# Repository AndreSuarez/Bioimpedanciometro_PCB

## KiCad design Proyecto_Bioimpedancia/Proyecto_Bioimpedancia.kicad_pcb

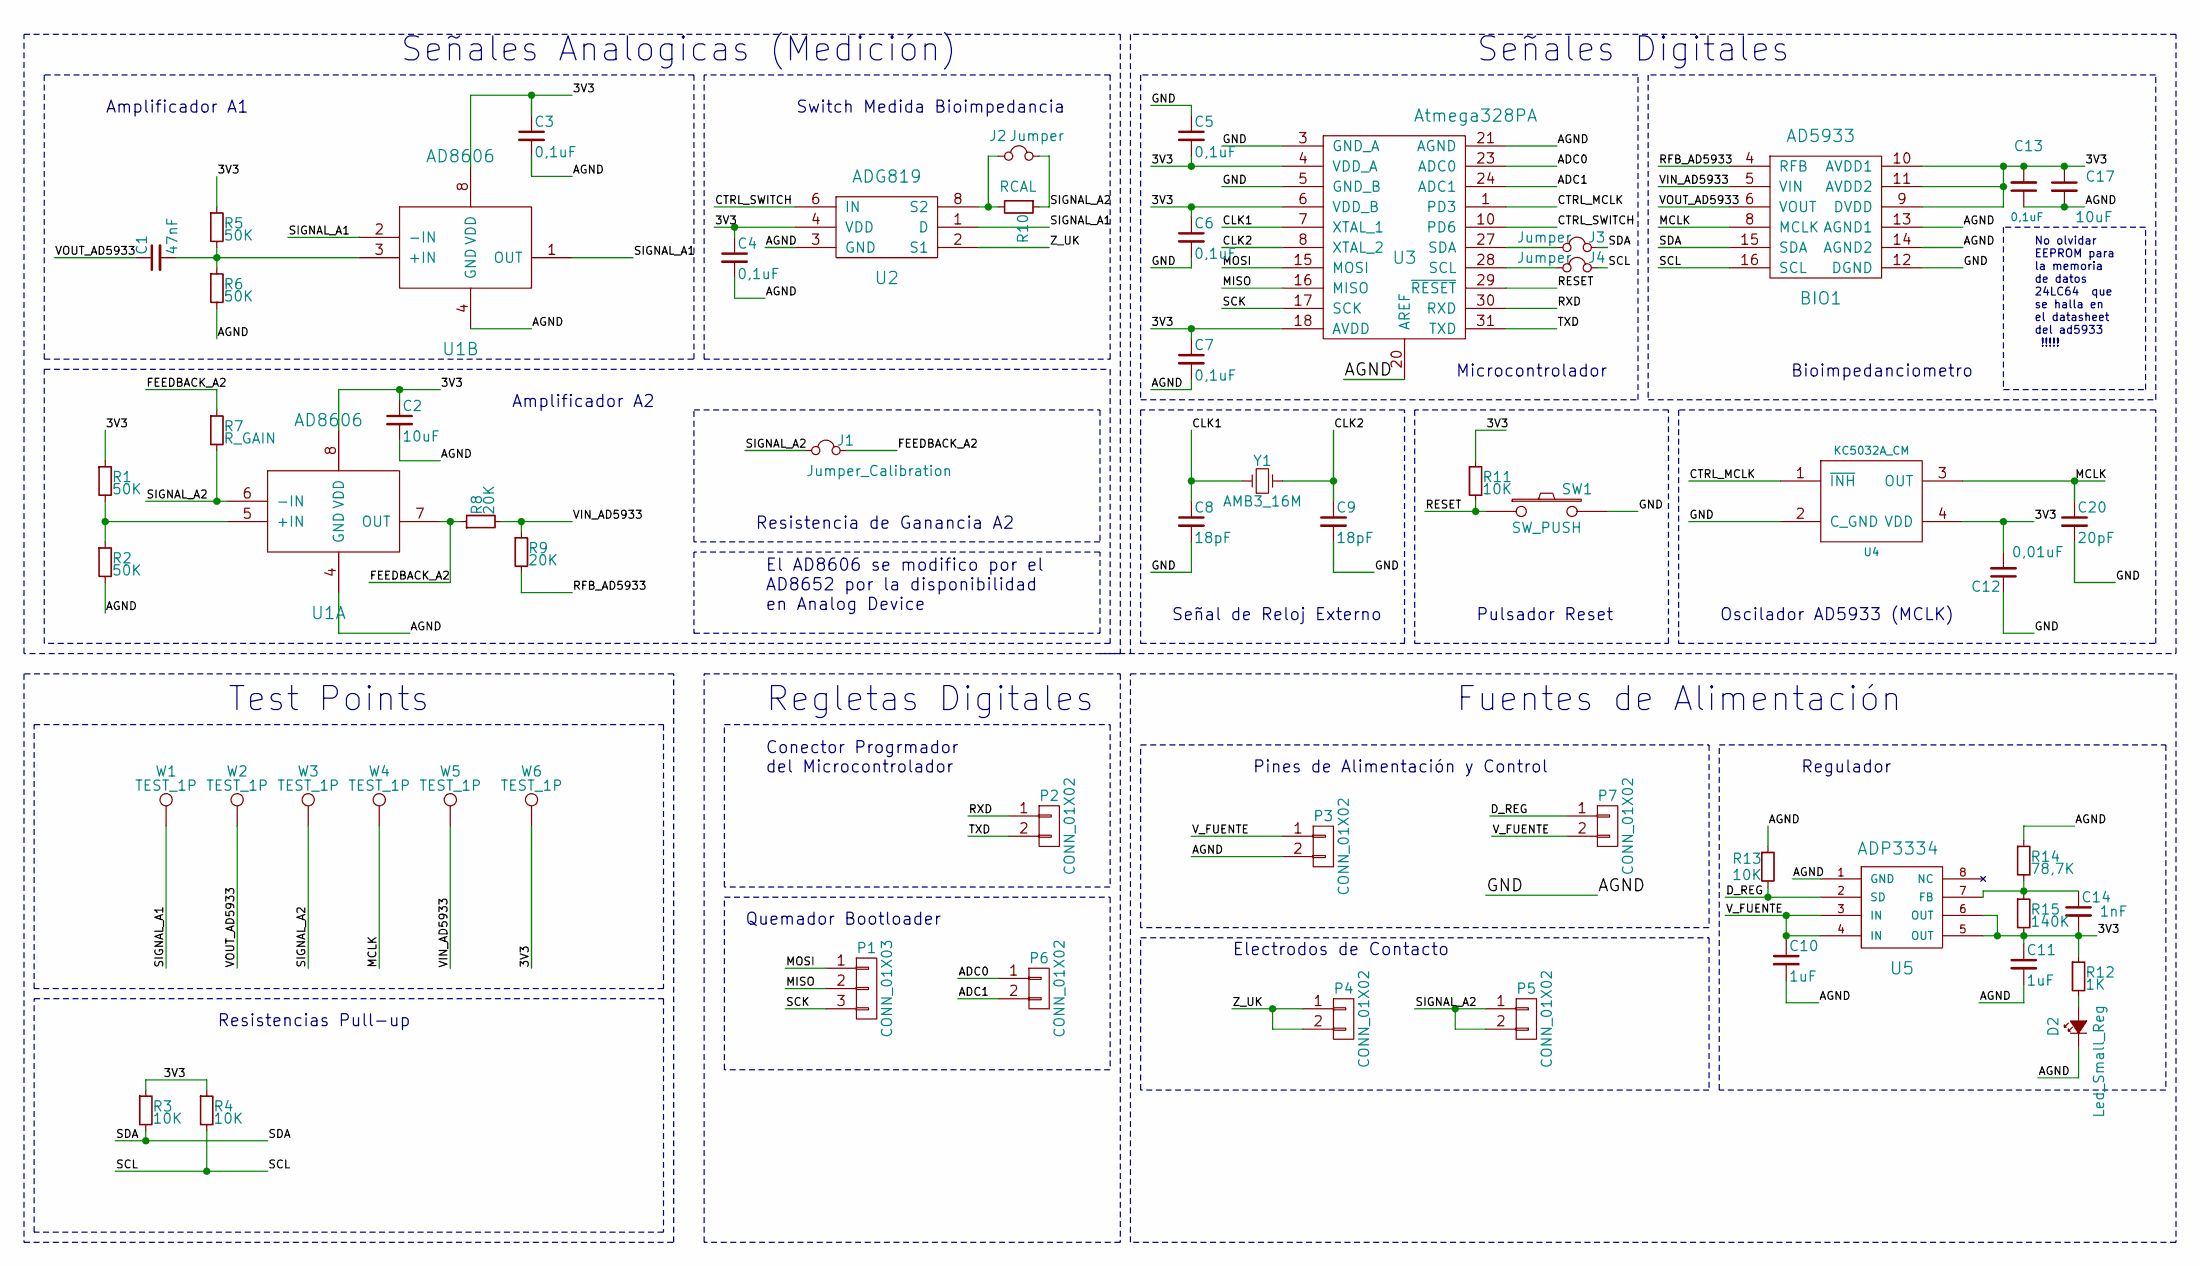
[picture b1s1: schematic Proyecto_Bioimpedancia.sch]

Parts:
BIO1: AD5933; SSOP-16_5.3x6.2mm_Pitch0.65mm
C1: 47nF; C_0805_HandSoldering
C2, C17: 10uF; C_0805_HandSoldering
C3, C4, C5, C6, C7, C13: 0,1uF; C_0805_HandSoldering
C8, C9: 18pF; C_0805_HandSoldering
C10, C11: 1uF; C_0805_HandSoldering
C12: 0,01uF; C_0805_HandSoldering
C14: 1nF; C_1206_HandSoldering
C20: 20pF; C_0805_HandSoldering
D2: Led_Small_Reg; LED_0805
J1: Jumper_Calibration; Pin_Header_Straight_1x02_Pitch2.54mm
J2, J3, J4: Jumper; Pin_Header_Straight_1x02_Pitch2.54mm
P1: CONN_01X03; Socket_Strip_Straight_1x03_Pitch2.54mm
P2, P3, P4, P5, P6, P7: CONN_01X02; Socket_Strip_Straight_1x02_Pitch2.54mm
R1, R2, R5, R6: 50K; R_0805_HandSoldering
R3, R4, R11, R13: 10K; R_0805_HandSoldering
R7: R_GAIN; R_0805_HandSoldering
R8, R9: 20K; R_0805_HandSoldering
R10: RCAL; R_0805_HandSoldering
R12: 1K; R_0805_HandSoldering
R14: 78,7K; R_0805_HandSoldering
R15: 140K; R_0805_HandSoldering
SW1: SW_PUSH; KPT_1187B
U1: AD8606; SOIC-8_3.9x4.9mm_Pitch1.27mm
U2: ADG819; MSOP-8_3x3mm_Pitch0.65mm
U3: Atmega328PA; TQFP-32_7x7mm_Pitch0.8mm
U4: KC5032A_CM
U5: ADP3334; SOIC-8_3.9x4.9mm_Pitch1.27mm
W1, W2, W3, W4, W5, W6: TEST_1P; Measurement_Point_Round-TH_Small
Y1: AMB3_16M; Crystal_SMD_Abracon_ABM3-2pin_5.0x3.2mm_HandSoldering

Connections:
/3V3: BIO1.9 (DVDD), BIO1.10 (AVDD1), BIO1.11 (AVDD2), C2.1, C3.1, C4.1, C5.2, C6.1, C7.1, C11.1, C12.2, C13.2, C14.2, C17.1, R1.1, R3.1, R4.1, R5.1, R11.1, R12.1, R15.2, U1.8 (VDD), U2.4 (VDD), U3.4 (VDD_A), U3.6 (VDD_B), U3.18 (AVDD), U4.4 (VDD), U5.5 (OUT), U5.6 (OUT), W6.1
/ADC0: P6.1, U3.23 (ADC0)
/ADC1: P6.2, U3.24 (ADC1)
/AGND: BIO1.12 (DGND), BIO1.13 (AGND1), BIO1.14 (AGND2), C2.2, C3.2, C4.2, C5.1, C6.2, C7.2, C8.2, C9.2, C10.2, C11.2, C12.1, C13.1, C17.2, C20.2, D2.1 (K), P3.2, R2.2, R6.2, R13.1, R14.1, SW1.2, U1.4 (GND), U2.3 (GND), U3.3 (GND_A), U3.5 (GND_B), U3.20 (AREF), U3.21 (AGND), U4.2 (C_GND), U5.1 (GND)
/CLK1: C8.1, U3.7 (XTAL_1), Y1.1
/CLK2: C9.1, U3.8 (XTAL_2), Y1.2
/CTRL_MCLK: U3.1 (PD3), U4.1 (~INH)
/CTRL_SWITCH: U2.6 (IN), U3.10 (PD6)
/D_REG: P7.1, R13.2, U5.2 (SD)
/FEEDBACK_A2: J1.1, R7.1, R8.1, U1.7 (OUT)
/MCLK: BIO1.8 (MCLK), C20.1, U4.3 (OUT), W4.1
/MISO: P1.2, U3.16 (MISO)
/MOSI: P1.1, U3.15 (MOSI)
/RESET: R11.2, SW1.1, U3.29 (~RESET)
/RFB_AD5933: BIO1.4 (RFB), R9.2
/RXD: P2.1, U3.30 (RXD)
/SCK: P1.3, U3.17 (SCK)
/SCL: BIO1.16 (SCL), J4.1, R4.2
/SDA: BIO1.15 (SDA), J3.1, R3.2
/SIGNAL_A1: U1.1 (OUT), U1.2 (-IN), U2.1 (D), W1.1
/SIGNAL_A2: J1.2, J2.1, P5.1, P5.2, R7.2, R10.1, U1.6 (-IN), W3.1
/TXD: P2.2, U3.31 (TXD)
/VIN_AD5933: BIO1.5 (VIN), R8.2, R9.1, W5.1
/VOUT_AD5933: BIO1.6 (VOUT), C1.1, W2.1
/V_FUENTE: C10.1, P3.1, P7.2, U5.3 (IN), U5.4 (IN)
/Z_UK: P4.1, P4.2, U2.2 (S1)
unnamed: C1.2, R5.2, R6.1, U1.3 (+IN)
unnamed: C14.1, R14.2, R15.1, U5.7 (FB)
unnamed: D2.2 (A), R12.2
unnamed: J2.2, R10.2, U2.8 (S2)
unnamed: J3.2, U3.27 (SDA)
unnamed: J4.2, U3.28 (SCL)
unnamed: R1.2, R2.1, U1.5 (+IN)

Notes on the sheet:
Señales Digitales
Fuentes de Alimentación
Regletas Digitales
Test Points
Señal de Reloj Externo
Pulsador Reset
Oscilador AD5933 (MCLK)
Bioimpedanciometro
Microcontrolador
Amplificador A1
Amplificador A2
Switch Medida Bioimpedancia
Quemador Bootloader
Conector Progrmador del Microcontrolador
Regulador
Pines de Alimentación y Control
Resistencias Pull-up
Señales Analogicas (Medición)
Electrodos de Contacto
Resistencia de Ganancia A2
No olvidar EEPROM para la memoria de datos 24LC64 que se halla en el datasheet del ad5933 !!!!!
El AD8606 se modifico por el AD8652 por la disponibilidad en Analog Device

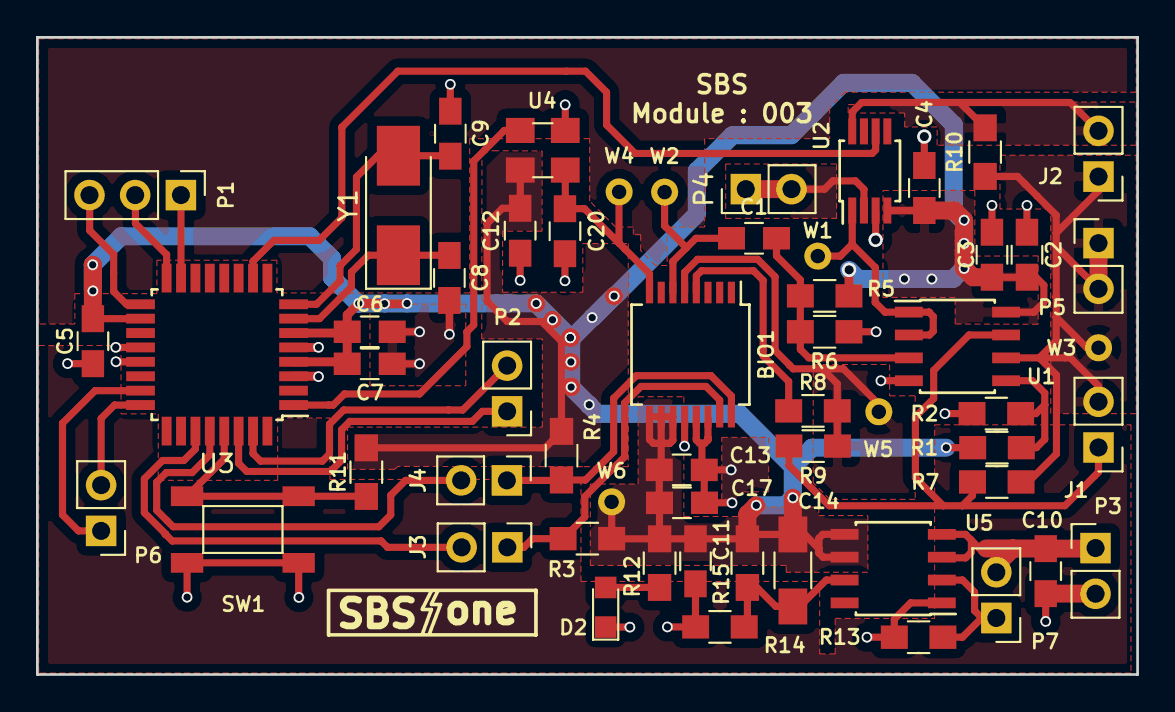
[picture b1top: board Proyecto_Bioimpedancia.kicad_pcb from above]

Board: 2 copper layers, 61.1 x 35.4 mm, 57 parts (0 on the bottom side), 33 nets.

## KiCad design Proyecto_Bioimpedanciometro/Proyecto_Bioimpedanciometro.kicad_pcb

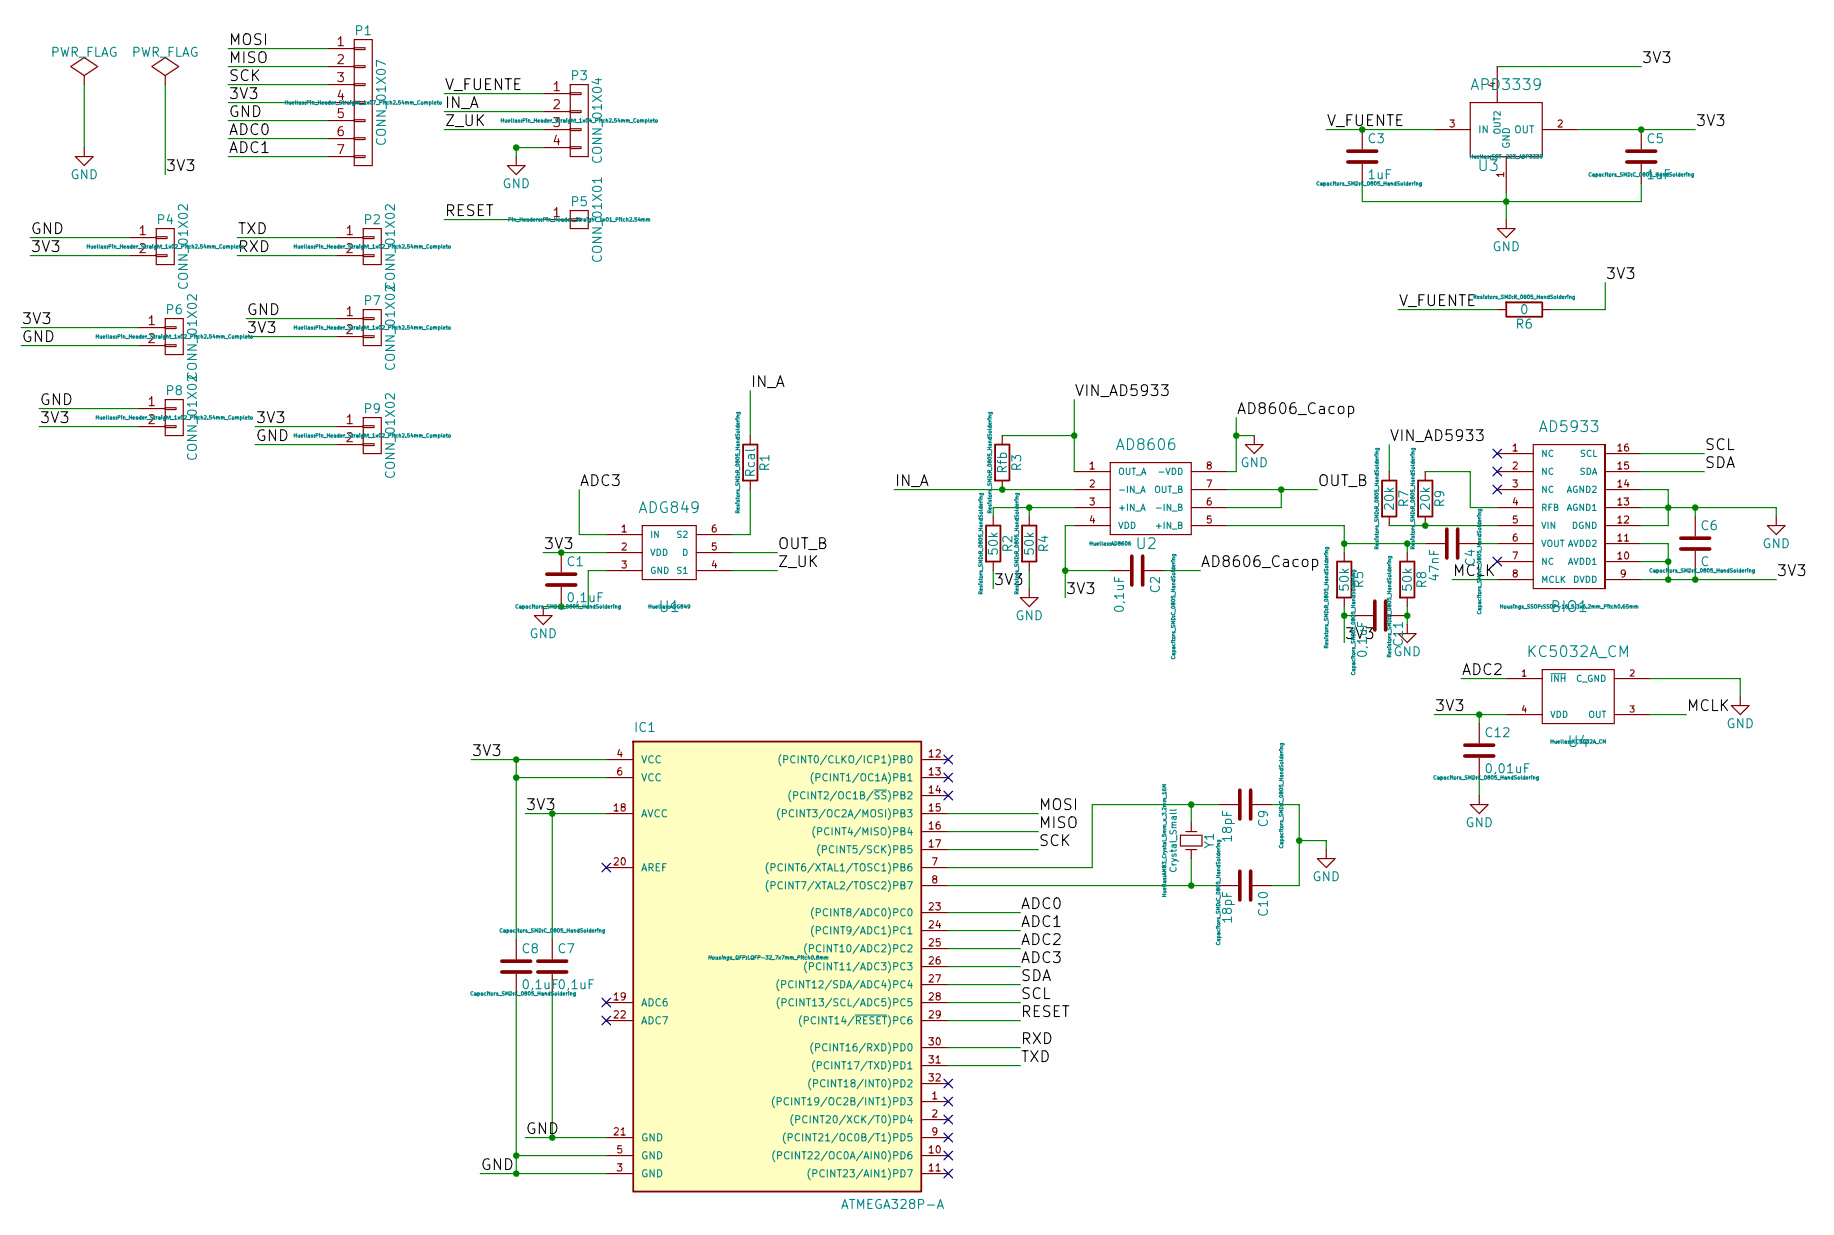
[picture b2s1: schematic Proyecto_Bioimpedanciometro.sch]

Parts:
BIO1: AD5933; SSOP-16_5.3x6.2mm_Pitch0.65mm
C1, C2, C7, C8, C11: 0,1uF; C_0805_HandSoldering
C3, C5: 1uF; C_0805_HandSoldering
C4: 47nF; C_0805_HandSoldering
C6: C; C_0805_HandSoldering
C9, C10: 18pF; C_0805_HandSoldering
C12: 0,01uF; C_0805_HandSoldering
IC1: ATMEGA328P-A; LQFP-32_7x7mm_Pitch0.8mm
P1: CONN_01X07; Pin_Header_Straight_1x07_Pitch2.54mm_Completo
P2, P4, P6, P7, P8, P9: CONN_01X02; Pin_Header_Straight_1x02_Pitch2.54mm_Completo
P3: CONN_01X04; Pin_Header_Straight_1x04_Pitch2.54mm_Completo
P5: CONN_01X01; Pin_Header_Straight_1x01_Pitch2.54mm
R1: Rcal; R_0805_HandSoldering
R2, R4, R5, R8: 50k; R_0805_HandSoldering
R3: Rfb; R_0805_HandSoldering
R6: 0; R_0805_HandSoldering
R7, R9: 20k; R_0805_HandSoldering
U1: ADG849
U2: AD8606
U3: APD3339; SOT-223_ADP3339
U4: KC5032A_CM
Y1: Crystal_Small; AMB3_Crystal_5mm_x_3,2mm_16M

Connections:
/3V3: BIO1.9 (DVDD), BIO1.10 (AVDD1), BIO1.11 (AVDD2), C1.1, C2.2, C5.1, C6.2, C7.1, C8.1, C11.2, C12.1, IC1.4 (VCC), IC1.6 (VCC), IC1.18 (AVCC), P1.4, P4.2, P6.1, P7.2, P8.2, P9.1, R2.2, R5.2, R6.1, U1.2 (VDD), U2.4 (VDD), U3.2 (OUT), U3.4 (OUT2), U4.4 (VDD)
/ADC0: IC1.23 ((PCINT8/ADC0)PC0), P1.6
/ADC1: IC1.24 ((PCINT9/ADC1)PC1), P1.7
/ADC2: IC1.25 ((PCINT10/ADC2)PC2), U4.1 (~INH)
/ADC3: IC1.26 ((PCINT11/ADC3)PC3), U1.1 (IN)
/IN_A: P3.2, R1.1, R3.2, U2.2 (-IN_A)
/MCLK: BIO1.8 (MCLK), U4.3 (OUT)
/MISO: IC1.16 ((PCINT4/MISO)PB4), P1.2
/MOSI: IC1.15 ((PCINT3/OC2A/MOSI)PB3), P1.1
/OUT_B: U1.5 (D), U2.6 (-IN_B), U2.7 (OUT_B)
/RESET: IC1.29 ((PCINT14/~RESET~)PC6), P5.1
/RXD: IC1.30 ((PCINT16/RXD)PD0), P2.2
/SCK: IC1.17 ((PCINT5/SCK)PB5), P1.3
/SCL: BIO1.16 (SCL), IC1.28 ((PCINT13/SCL/ADC5)PC5)
/SDA: BIO1.15 (SDA), IC1.27 ((PCINT12/SDA/ADC4)PC4)
/TXD: IC1.31 ((PCINT17/TXD)PD1), P2.1
/VIN_AD5933: R3.1, R7.1, U2.1 (OUT_A)
/V_FUENTE: C3.1, P3.1, R6.2, U3.3 (IN)
/Z_UK: P3.3, U1.4 (S1)
GND: BIO1.12 (DGND), BIO1.13 (AGND1), BIO1.14 (AGND2), C1.2, C2.1, C3.2, C5.2, C6.1, C7.2, C8.2, C9.1, C10.1, C11.1, C12.2, IC1.3 (GND), IC1.5 (GND), IC1.21 (GND), P1.5, P3.4, P4.1, P6.2, P7.1, P8.1, P9.2, R4.2, R8.2, U1.3 (GND), U2.8 (-VDD), U3.1 (GND), U4.2 (C_GND)
unnamed: BIO1.4 (RFB), R9.1
unnamed: BIO1.5 (VIN), R7.2, R9.2
unnamed: BIO1.6 (VOUT), C4.1
unnamed: C4.2, R5.1, R8.1, U2.5 (+IN_B)
unnamed: C9.2, IC1.7 ((PCINT6/XTAL1/TOSC1)PB6), Y1.1
unnamed: C10.2, IC1.8 ((PCINT7/XTAL2/TOSC2)PB7), Y1.2
unnamed: R1.2, U1.6 (S2)
unnamed: R2.1, R4.1, U2.3 (+IN_A)

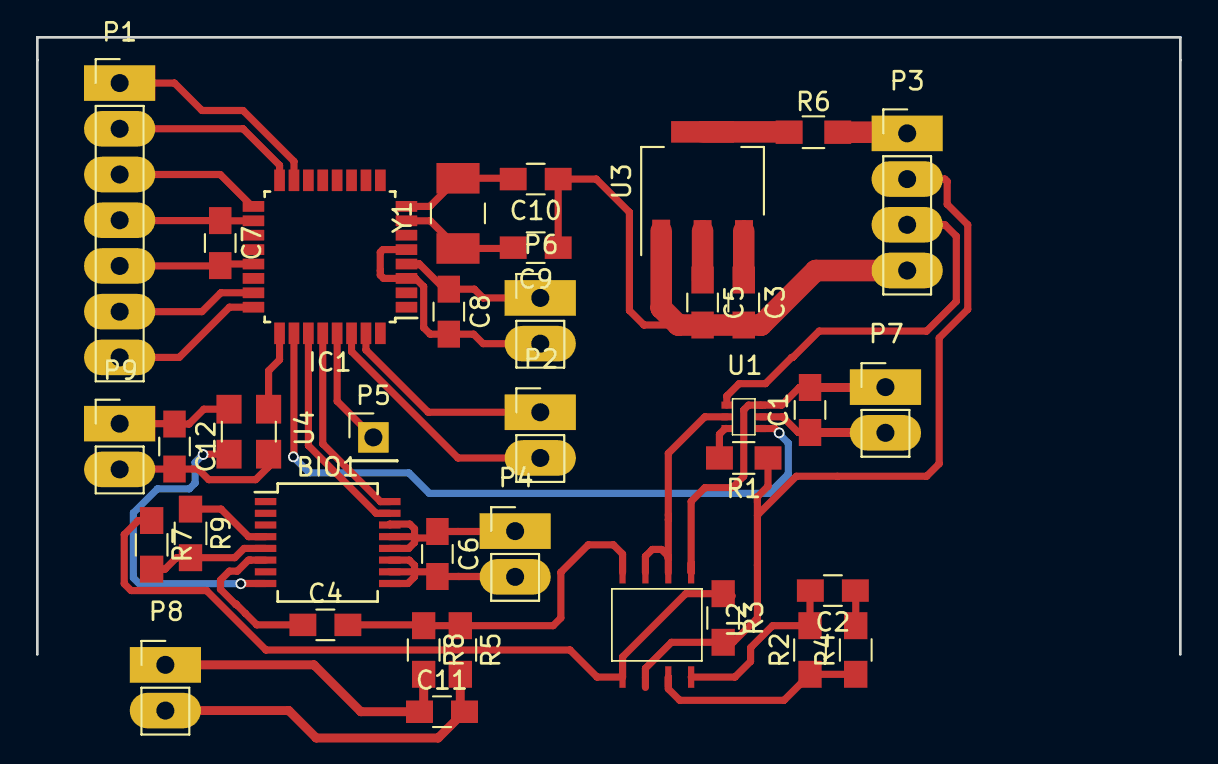
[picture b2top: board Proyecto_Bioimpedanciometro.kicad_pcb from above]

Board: 2 copper layers, 63.5 x 34.3 mm, 37 parts (0 on the bottom side), 28 nets.

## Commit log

2017-05-05 Primera version
    Hola Mundo
2017-05-06 Segunda Version
    Empieza PCB
2017-05-06 Tercera Version
    Revisar conexion bajo el micro, se hizo teniendo en cuenta simetria
    segun lo hablado.
2017-05-07 Cuarta Versión
    Revisar todo el diseño y errores mas importantes
2017-05-07 Diseño a corregir
2017-05-08 Adición del Oscilador con huella y esquematico de medidas personalizadas
    Diseño sacado de otros datasheet, con valor de capacitancia recomendado
    para la propia referencia
2017-05-09 Esquematico personalizado
    Nuevo esquematico con huellas
2017-05-09 Esquematico con Huellas
    Anexado huella pulsador
2017-05-09 Dibujo Esquematico Bloque Bioimpedancia
    Diagrama completo Bioimpedancia
2017-05-10 Esquematico Actualizado
    Cambios Sugeridos y división en sub-bloques
2017-05-10 Diseño Mejorado 10/05/2017
    Diagrama mas explicativo con señales mas claras
2017-05-12 Segregación Bioimpedanciometro
    Faltaria el cambio del regulador
2017-05-15 Layout casi terminado
    Faltan tierras y polarización solamente
2017-05-16 PCB Final
    Falta ultima revisión Esquematico
2017-05-16 Isletas añadidas a PCB
    Revisar isletas
2017-05-16 Final Diseño
2017-05-16 VersionFinal 2.0
2017-05-17 Version con BOM File aprobado
    Falta solo la RAM
2017-05-17 Version 17 Mayo
    Con plano de tierra
2017-05-18 Vias corregidas
    Falta regulador
2017-05-18 Muescas para asegurar a la carcasa anexadas
    Diseño Final Preliminar
2017-05-18 Diseño Final con Planos Expandidos
    Diseño 18 de Mayo
2017-05-22 Ultima versión para impresión
    Final
2017-10-01 Libreria actualizada
